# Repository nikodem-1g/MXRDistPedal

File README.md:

MXR Distortion Plus pedal project

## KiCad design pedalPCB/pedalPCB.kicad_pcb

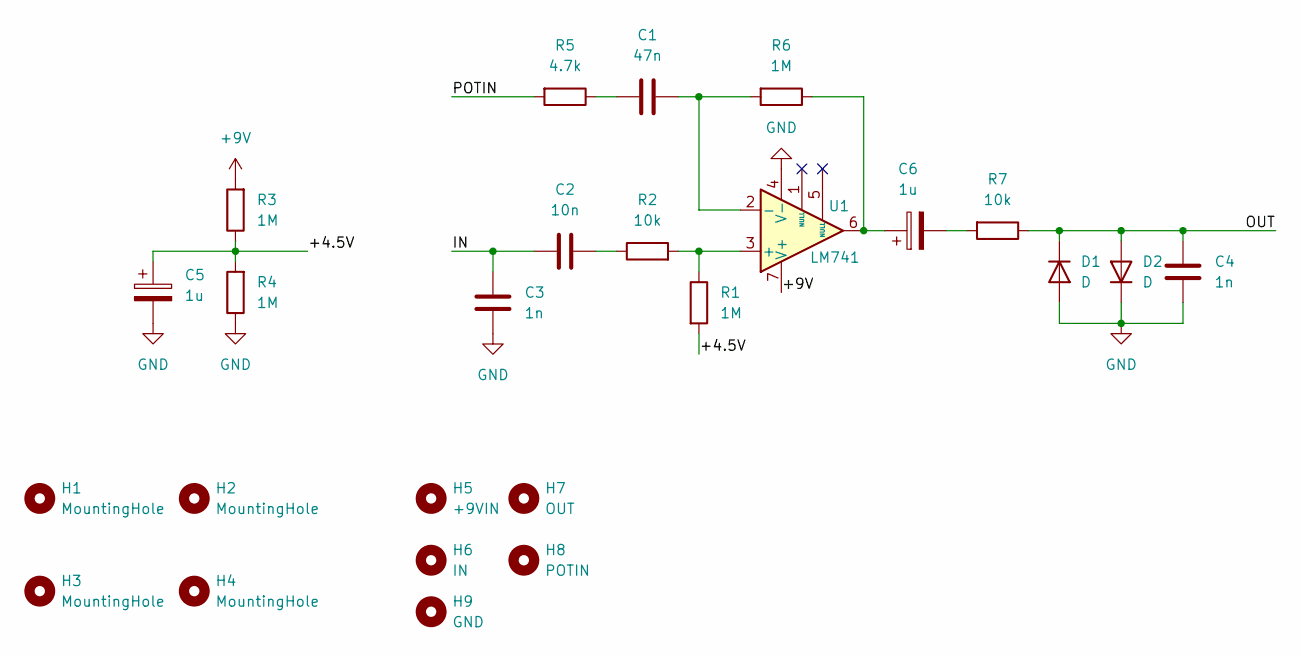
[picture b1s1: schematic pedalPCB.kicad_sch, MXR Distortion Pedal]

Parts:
C1: 47n; ECWH8473HA
C2: 10n; ECWH8103HA
C3, C4: 1n; WHA3C102JF7
C5, C6: 1u; CP_Radial_D6.3mm_P2.50mm
D1, D2: D; D_DO-35_SOD27_P7.62mm_Horizontal
H1, H2, H3, H4: MountingHole; MountingHole_3.2mm_M3
H5: +9VIN; MountingHole_3.5mm_Pad
H6: IN; MountingHole_3.5mm_Pad
H7: OUT; MountingHole_3.5mm_Pad
H8: POTIN; MountingHole_3.5mm_Pad
H9: GND; MountingHole_3.5mm_Pad
R1, R3, R4, R6: 1M; R_Axial_DIN0207_L6.3mm_D2.5mm_P10.16mm_Horizontal
R2, R7: 10k; R_Axial_DIN0207_L6.3mm_D2.5mm_P10.16mm_Horizontal
R5: 4.7k; R_Axial_DIN0207_L6.3mm_D2.5mm_P10.16mm_Horizontal
U1: LM741; DIP-8_W7.62mm_Socket_LongPads

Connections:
+9V: R3.2, U1.7 (V+)
/+4.5V: C5.1, R1.2, R3.1, R4.2
/IN: C2.1, C3.2
/OUT: C4.2, D1.1 (K), D2.2 (A), R7.1
/POTIN: R5.2
GND: C3.1, C4.1, C5.2, D1.2 (A), D2.1 (K), R4.1, U1.4 (V-)
unnamed: C1.1, R5.1
unnamed: C2.2, R2.1
unnamed: C6.1, R6.1, U1.6
unnamed: C6.2, R7.2
unnamed: R1.1, R2.2, U1.3 (+)
unnamed: C1.2, R6.2, U1.2 (-)

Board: 2 copper layers, 25 parts (0 on the bottom side), 11 nets, no tracks yet.
